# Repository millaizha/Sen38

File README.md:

# Sen38

The Sen38 is 38-key split column stagger keyboard with pinky splay. 
Made using [ergogen](https://ergogen.xyz)

This keyboard is MX and Choc compatible.

## Notes

* .yaml does not include edge cuts. May need to add it in KiCAD.
* Changed some placements of the diodes in KiCAD.
* Will try to make the connections look better soon.
* Firmware to be added soon in my [QMK fork](https://github.com/millaizha/qmk_firmware).

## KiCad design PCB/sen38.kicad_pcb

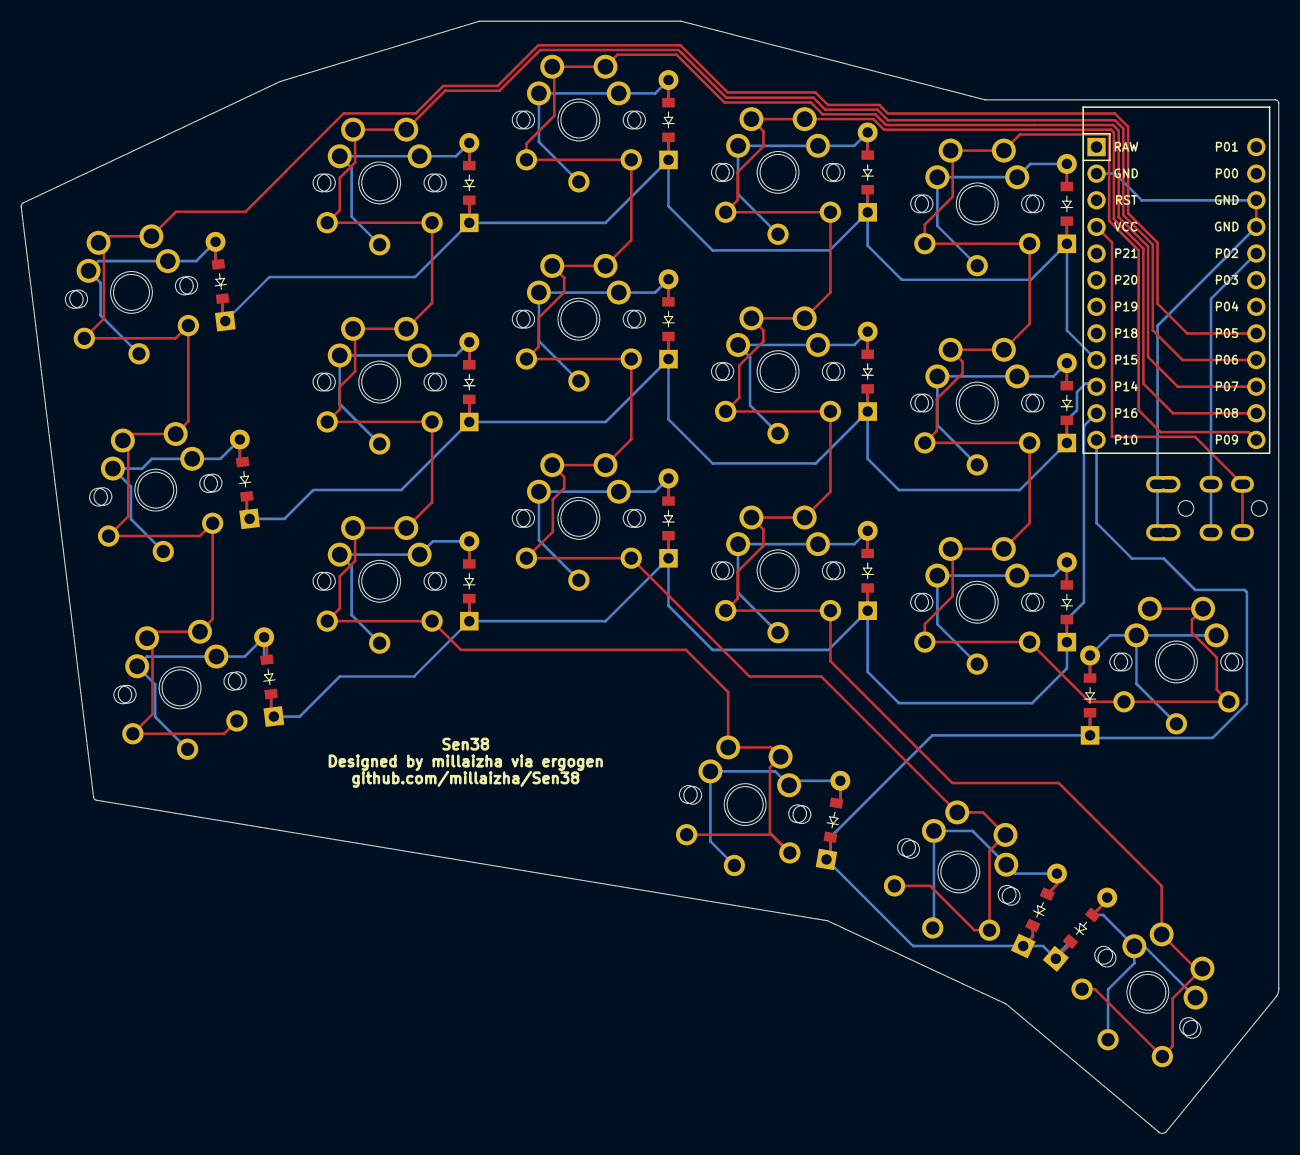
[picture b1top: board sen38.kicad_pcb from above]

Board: 2 copper layers, 120.0 x 106.1 mm, 58 parts (0 on the bottom side), 29 nets.

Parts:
D1, D2, D3, D4, D5, D6, D7, D8, D9, D10, D11, D12, D13, D14, D15, D16, D17, D18, D19: ComboDiode
MCU1: ProMicro
S1, S3, S5, S7, S9, S11, S13, S15, S17, S19, S21, S23, S25, S27, S29, S31, S33, S35, S37: MX
S2, S4, S6, S8, S10, S12, S14, S16, S18, S20, S22, S24, S26, S28, S30, S32, S34, S36, S38: PG1350

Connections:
GND: MCU1.2, MCU1.15, MCU1.16
P5: MCU1.20, S1.1, S2.1, S3.1, S4.1, S5.1, S6.1
P6: MCU1.21, S7.1, S8.1, S9.1, S10.1, S11.1, S12.1, S31.1, S32.1
P7: MCU1.22, S13.1, S14.1, S15.1, S16.1, S17.1, S18.1, S33.1, S34.1
P8: MCU1.23, S19.1, S20.1, S21.1, S22.1, S23.1, S24.1, S35.1, S36.1
P9: MCU1.24, S25.1, S26.1, S27.1, S28.1, S29.1, S30.1, S37.1, S38.1
P10: D16.1, D16.2, D17.1, D17.2, D18.1, D18.2, D19.1, D19.2, MCU1.12
P14: D2.1, D2.2, D5.1, D5.2, D8.1, D8.2, D11.1, D11.2, D14.1, D14.2, MCU1.10
P15: D3.1, D3.2, D6.1, D6.2, D9.1, D9.2, D12.1, D12.2, D15.1, D15.2, MCU1.9
P16: D1.1, D1.2, D4.1, D4.2, D7.1, D7.2, D10.1, D10.2, D13.1, D13.2, MCU1.11
bottom_home: D19.1, D19.2, S37.2, S38.2
far_home: D18.1, D18.2, S35.2, S36.2
home_home: D17.1, D17.2, S33.2, S34.2
index_bottom: D10.1, D10.2, S19.2, S20.2
index_home: D11.1, D11.2, S21.2, S22.2
index_top: D12.1, D12.2, S23.2, S24.2
inner_bottom: D13.1, D13.2, S25.2, S26.2
inner_home: D14.1, D14.2, S27.2, S28.2
inner_top: D15.1, D15.2, S29.2, S30.2
middle_bottom: D7.1, D7.2, S13.2, S14.2
middle_home: D8.1, D8.2, S15.2, S16.2
middle_top: D9.1, D9.2, S17.2, S18.2
near_home: D16.1, D16.2, S31.2, S32.2
pinky_bottom: D1.1, D1.2, S1.2, S2.2
pinky_home: D2.1, D2.2, S3.2, S4.2
pinky_top: D3.1, D3.2, S5.2, S6.2
ring_bottom: D4.1, D4.2, S7.2, S8.2
ring_home: D5.1, D5.2, S9.2, S10.2
ring_top: D6.1, D6.2, S11.2, S12.2
